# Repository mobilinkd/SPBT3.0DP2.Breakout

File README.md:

# SPBT3.0DP2.Breakout
ST SPBT3.0DP2 Bluetooth 3.0 Module Breakout Board

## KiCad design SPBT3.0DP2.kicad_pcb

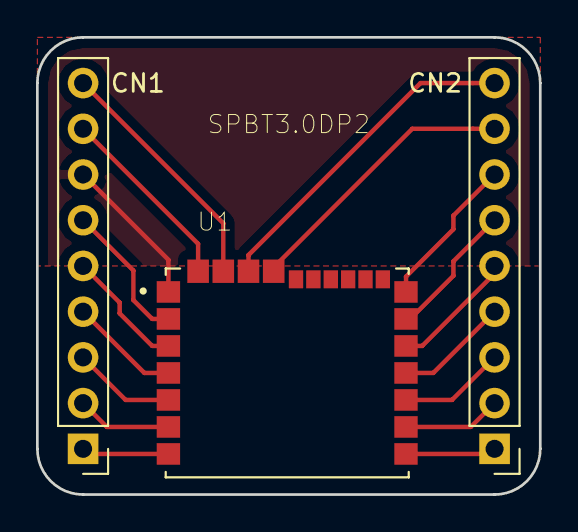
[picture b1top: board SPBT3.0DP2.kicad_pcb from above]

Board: 2 copper layers, 27.9 x 25.4 mm, 3 parts (0 on the bottom side), 18 nets.

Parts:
CN1, CN2: CONN_01X09; Pin_Header_Straight_1x09_Pitch2.54mm
U1: SPBT3.0DP2; STMICRO_SPBT3.0DP2

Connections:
unnamed: CN1.1, U1.7
unnamed: CN1.2, U1.6
unnamed: CN1.3, U1.5
unnamed: CN1.4, U1.4
unnamed: CN1.5, U1.3
unnamed: CN1.6, U1.2
unnamed: CN1.7, U1.1
unnamed: CN1.8, U1.18
unnamed: CN1.9, U1.17
unnamed: CN2.1, U1.8
unnamed: CN2.2, U1.9
unnamed: CN2.3, U1.10
unnamed: CN2.4, U1.11
unnamed: CN2.5, U1.12
unnamed: CN2.6, U1.13
unnamed: CN2.7, U1.14
unnamed: CN2.8, U1.15
unnamed: CN2.9, U1.16

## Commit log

2018-06-18 Initial module implementation.
2018-06-19 Fix mask clearance. Set to 0.
2018-06-19 Add gerber files.
